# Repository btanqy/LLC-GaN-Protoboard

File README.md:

# LLC-GaN-Protoboard

This board will be a prototype GaN based LLC converter, with a target rating of 80W with 24V input to 400V output, ideally for renewable power conversion and high voltage applications in plasma generation. 

This board will be controlled by and mounted on top of the [LAUNCHXL-F28P55X](https://www.digikey.com/en/products/detail/texas-instruments/LAUNCHXL-F28P55X/22674628). It will be based on the reference design for TIDA-010062, minus the PFC element.

The board is made in KiCad while the code is done in Code Composer Studio by TI. 

Some resources that were used for reference during board design:
- [Pinout Map](https://www.ti.com/lit/ml/spaz056/spaz056.pdf?ts=1783172662507)
- [LaunchPad Hardware Design Guidelines](https://www.ti.com/lit/an/slaa542/slaa542.pdf)
- [F28P55X Datasheet](https://www.ti.com/lit/ds/sprsp85d/sprsp85d.pdf?ts=1783173915619)
- [Open Magnetics](https://openmagnetics.com)

- [LLC Topology](https://e2e.ti.com/cfs-file/__key/communityserver-discussions-components-files/196/Ch4.pdf)
- [LLC Switches and Tank](https://www.monolithicpower.com/learning/resources/understanding-llc-operation-part-i-power-switches-and-resonant-tank)
- [Example LLC Design](https://www.infineon.com/assets/row/public/documents/24/42/infineon-design-example-resonant-llc-converter-operation-and-design-applicationnotes-en.pdf)

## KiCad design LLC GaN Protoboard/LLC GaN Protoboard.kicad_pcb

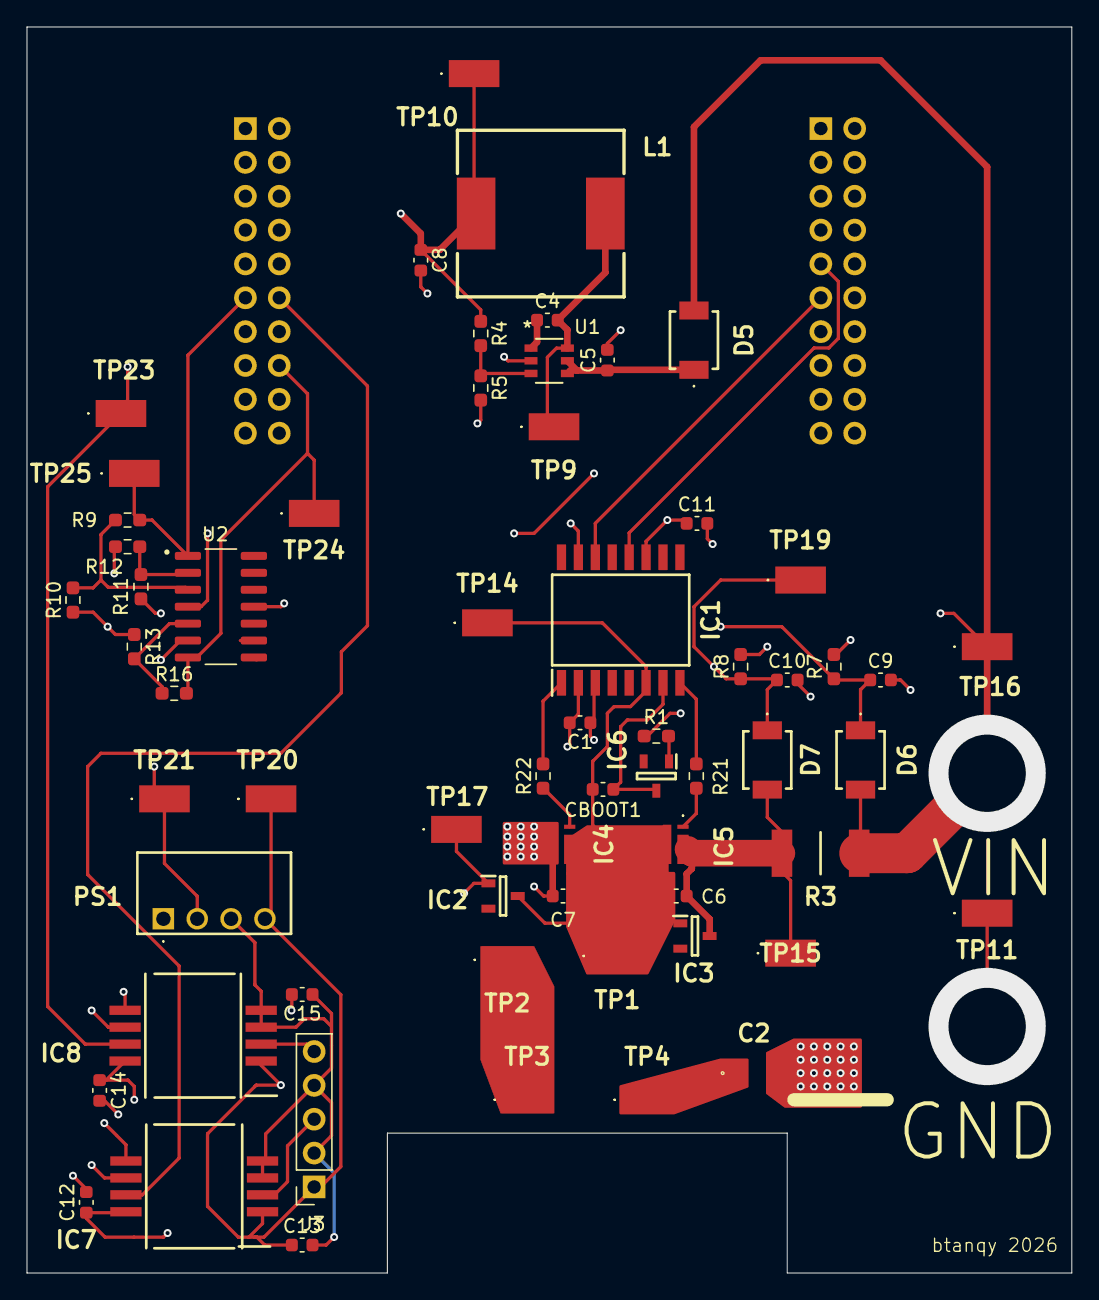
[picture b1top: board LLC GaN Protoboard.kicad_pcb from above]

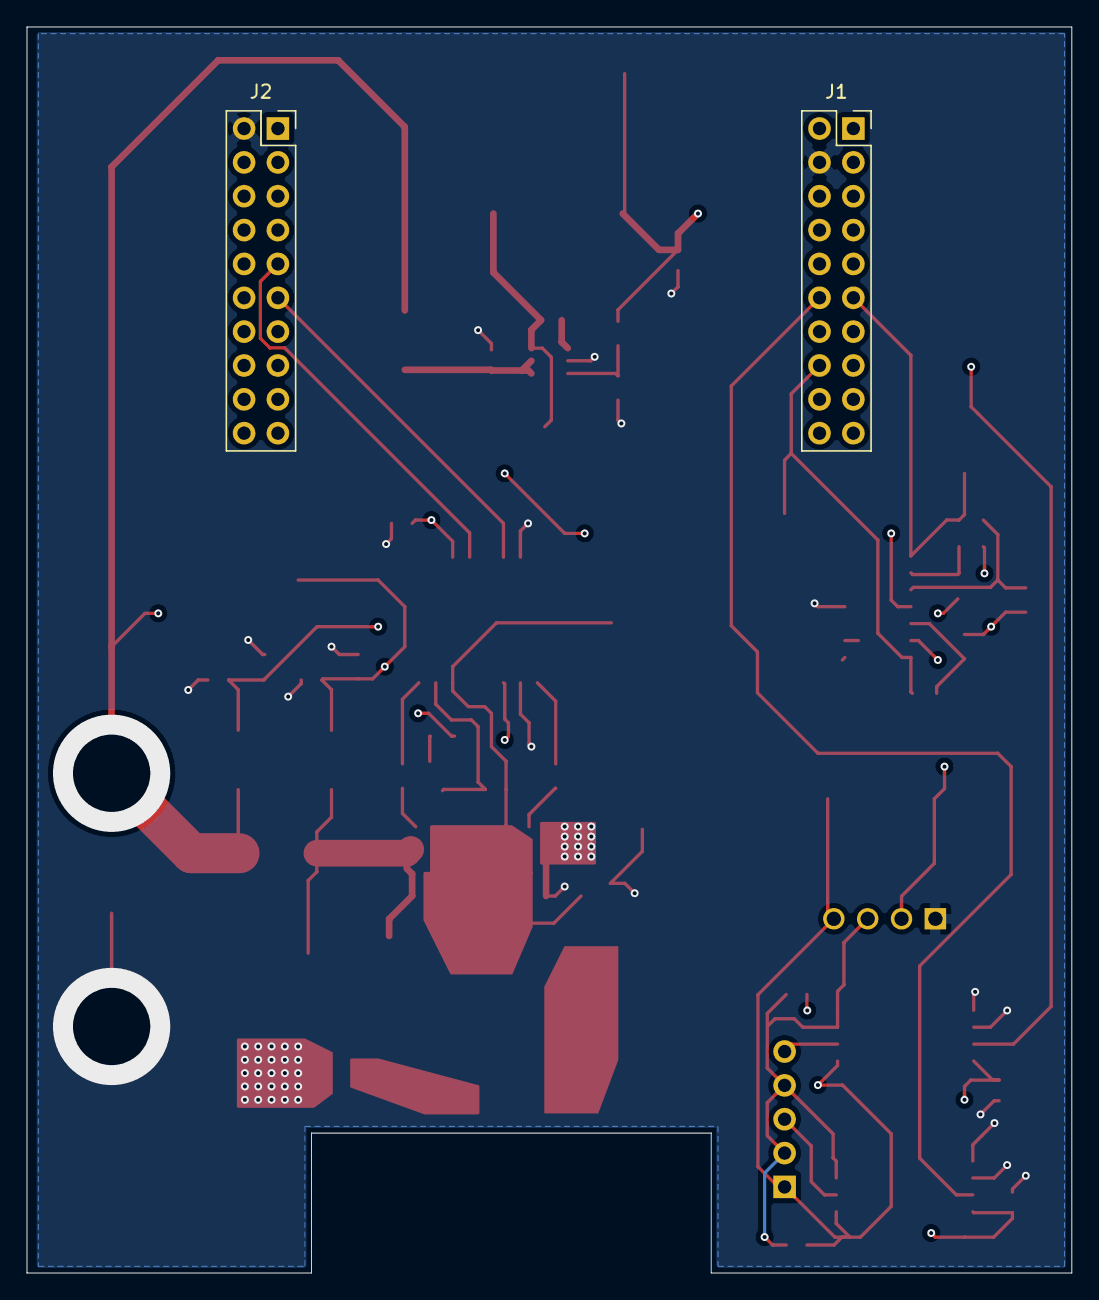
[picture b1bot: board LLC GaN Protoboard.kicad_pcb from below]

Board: 4 copper layers, 78.4 x 93.5 mm, 64 parts (2 on the bottom side), 31 nets.

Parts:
C1, C6, C7: 1u; C_0603_1608Metric
C2: C1206C302JCGACTU; C1206
C4: .1u; C_0603_1608Metric
C5: 2.2u; C_0603_1608Metric
C8: 22u; C_0603_1608Metric
C9, C10: 1n; C_0603_1608Metric
C11, C12, C13, C14, C15: 0.1u; C_0603_1608Metric
CBOOT1: C; C_0603_1608Metric
D5, D6, D7: ADS12B3-ASARH; ADS12B3ASARH
IC1: FAN73912AMX; SOIC127P1032X264-16N
IC2, IC3, IC6: BZX84-C5V6,215; SOT95P230X110-3N
IC4, IC5: GAN7R0-150LBE; GAN7R0150LBE
IC7, IC8: AMC1200SDUBR; SOP254P1040X485-8N
J1, J2: Conn_02x10_Odd_Even; PinSocket_2x10_P2.54mm_Vertical
J3: Conn_01x05_Pin; PinSocket_1x05_P2.54mm_Vertical
L1: SRR1260-150M
PS1: CME0303S3C
R1: 5; R_0603_1608Metric_Pad0.98x0.95mm_HandSolder
R3: CRA2512-FZ-R050ELF; RESC6434X90N
R4: 118k; R_0603_1608Metric_Pad0.98x0.95mm_HandSolder
R5: 22.1k; R_0603_1608Metric_Pad0.98x0.95mm_HandSolder
R7, R8: 1k; R_0603_1608Metric_Pad0.98x0.95mm_HandSolder
R9, R10, R11, R12, R13, R16: 10k; R_0603_1608Metric_Pad0.98x0.95mm_HandSolder
R21, R22: 1; R_0603_1608Metric_Pad0.98x0.95mm_HandSolder
TP1, TP2, TP3, TP4, TP9, TP10, TP11, TP14, TP15, TP16, TP17, TP19, TP20, TP21, TP23, TP24, TP25: 5019
U1: PLMR54410DBVR; U_SOT-23_TEX
U2: LM124DR; SOIC127P600X175-14N

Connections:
+3.3V: C11.1, C12.1, C14.1, IC1.11 (VDD), IC7.8 (VDD2), IC8.8 (VDD2), J1.1, PS1.2 (+VIN), R12.2, TP21.1 (1_1), U2.6 (2IN-)
+3.3V_ISO: C13.1, C15.2, IC7.1 (VDD1), IC8.1 (VDD1), J3.1, PS1.4 (+VOUT), TP20.1 (1_1)
+5V: C1.1, C8.1, IC1.3 (VCC), J1.2, L1.1, R1.1, R4.1, TP10.1 (1_1)
/LLC/FB: R4.2, R5.1, U1.3 (FB)
/LLC/GHIGH: IC1.8 (HO), R21.2
/LLC/GLOW: IC1.1 (LO), R22.2
/LLC/IIN_LOW: C6.2, D7.2 (A), IC3.3 (K), IC5.3 (D), R3.1, TP15.1 (1_1)
/LLC/IOUT_HIGH: IC7.2 (VINP), J3.3
/LLC/VB: CBOOT1.1, IC1.7 (VB), IC6.3 (K)
/LLC/VIN: D5.2 (A), D6.2 (A), R3.2, TP16.1 (1_1), U2.4 (VCC)
/LLC/VIN_RECT: C5.1, D5.1 (K), U1.4 (EN), U1.5 (VIN)
/LLC/VS: C6.1, C7.2, CBOOT1.2, IC1.6 (VS), IC2.3 (K), IC3.1 (A), IC4.3 (D), IC5.2 (S), TP1.1 (1_1), TP14.1 (1_1)
/Mount/ADCINB4/VOUT: IC8.7 (VOUTP), J1.14, TP23.1 (1_1)
/Sense/1IN+: R9.1, R10.2, U2.3 (1IN+)
/Sense/1IN-: R11.2, R12.1, U2.2 (1IN-)
/Sense/1OUT: J1.11, R9.2, TP25.1 (1_1), U2.1 (1OUT)
/Sense/2IN+: R13.2, R16.1, U2.5 (2IN+)
/Sense/2OUT: J1.16, R16.2, TP24.1 (1_1), U2.7 (2OUT)
/Sense/INV_HIGH: C9.1, D6.1 (K), R7.1, R10.1, R13.1
/Sense/INV_LOW: C10.1, D7.1 (K), R8.1, R11.1, TP19.1 (1_1)
/Sense/IOUT_VOUTP: IC7.7 (VOUTP), J1.12
/Sense/VINP: IC8.2 (VINP), J3.5
GND: C1.2, C2.2, C5.2, C7.1, C8.2, C9.2, C10.2, C11.2, C12.2, C14.2, IC1.2 (COM), IC1.15 (VSS), IC2.1 (A), IC4.2 (S), IC7.5 (GND2), IC7.6 (VOUTN), IC8.5 (GND2), IC8.6 (VOUTN), J1.4, J2.2, PS1.1 (-VIN), R5.2, R7.2, R8.2, TP11.1 (1_1), TP17.1 (1_1), U1.2 (GND), U2.11 (GND)
GND_ISO: C13.2, C15.1, IC7.3 (VINN), IC7.4 (GND1), IC8.3 (VINN), IC8.4 (GND1), J3.2, J3.4, PS1.3 (-VOUT)
unnamed: C2.1, TP4.1 (1_1)
unnamed: IC4.1 (G), R22.1
unnamed: IC5.1 (G), R21.1
unnamed: IC6.1 (A), R1.2
unnamed: TP2.1 (1_1), TP3.1 (1_1)
unnamed: C4.1, U1.1 (CB)
unnamed: C4.2, L1.2, TP9.1 (1_1), U1.6 (SW)

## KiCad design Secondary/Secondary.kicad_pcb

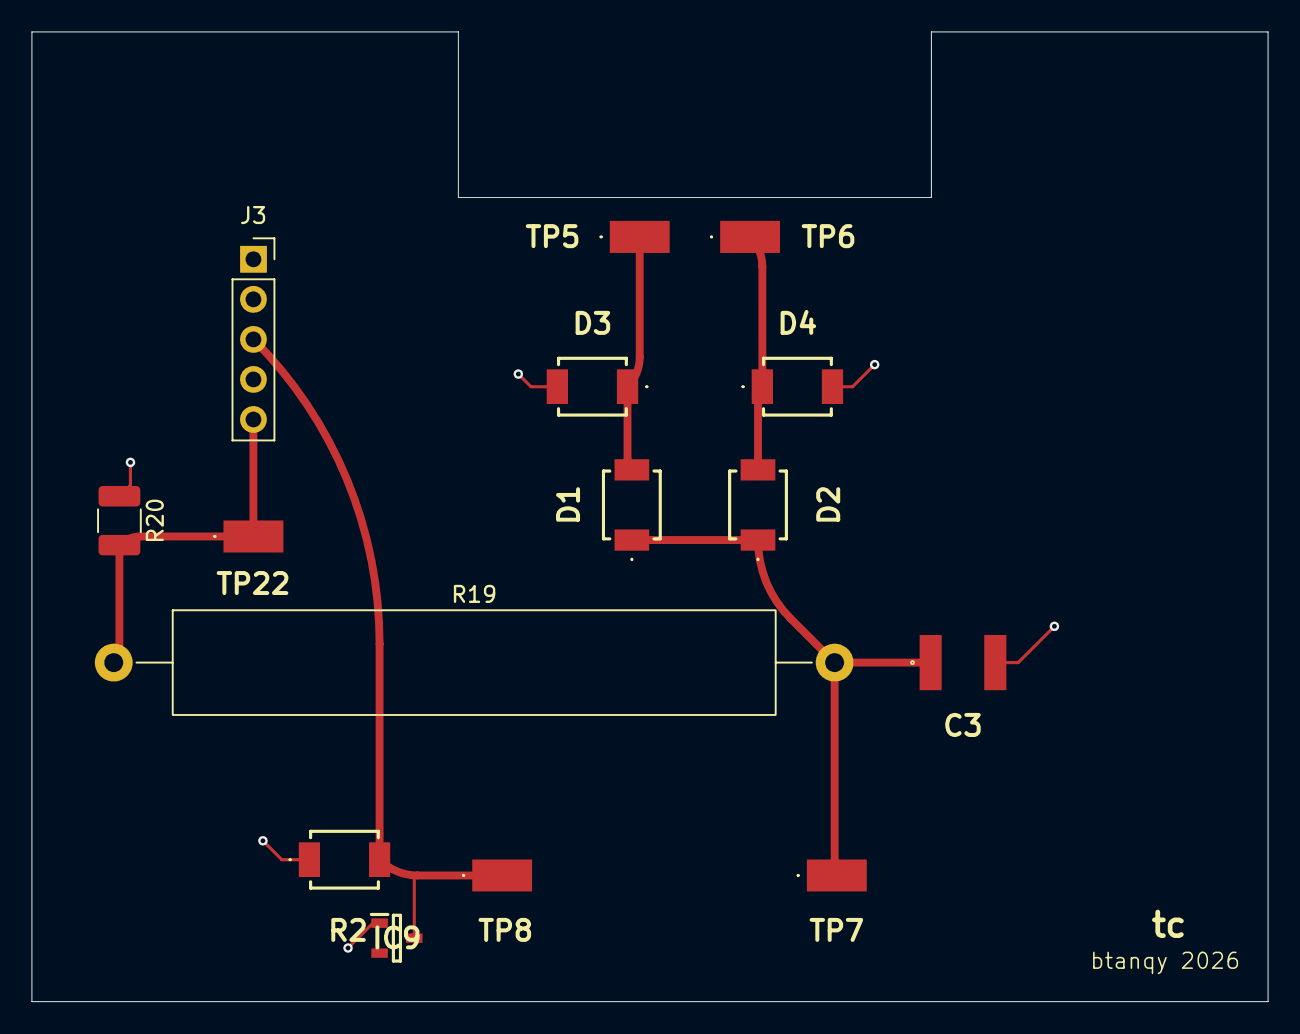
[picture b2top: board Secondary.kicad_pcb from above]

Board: 4 copper layers, 78.4 x 61.5 mm, 15 parts (0 on the bottom side), 6 nets.

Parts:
C3: C1812C104KDRACTU; C1812
D1, D2, D3, D4: ADS12B3-ASARH; ADS12B3ASARH
IC9: BZX84-C5V6,215; SOT95P230X110-3N
J3: Conn_01x05_Pin; PinSocket_1x05_P2.54mm_Vertical
R2: WSC25155R000FEA; ADS12B3ASARH
R19: 90k; R_Axial_Power_L38.0mm_W6.4mm_P45.72mm
R20: 1k; R_1210_3225Metric_Pad1.30x2.65mm_HandSolder
TP5, TP6, TP7, TP8, TP22: 5019

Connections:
/IOUT_HIGH: IC9.3 (K), J3.3, R2.2, TP8.1 (1_1)
/VOUT: C3.1, D1.1 (K), D2.1 (K), R19.2, TP7.1 (1_1)
GND_ISO: C3.2, D3.2 (A), D4.2 (A), IC9.1 (A), J3.2, J3.4, R2.1, R20.1
unnamed: D1.2 (A), D3.1 (K), TP5.1 (1_1)
unnamed: D2.2 (A), D4.1 (K), TP6.1 (1_1)
unnamed: J3.5, R19.1, R20.2, TP22.1 (1_1)
